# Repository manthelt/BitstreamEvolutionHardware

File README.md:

Bitstream Evolution Dev Board
===
###### Created by Logan Manthey ( [@manthelt](https://github.com/manthelt) )
---

## Introduction

This development board is an extension of the evolvable hardware open source project (https://evolvablehardware.org/). It was created to expand and bring new features to the evolvable hardware ecosystem while still maintaining it’s accessibility. To make the board accessible KiCAD was chosen for the CAD software given it’s open source and free nature. To find Gerber files for printing take a look at the release section. 

## Features

* **Multi-Channel ADC** 
Supporting two 8 channel **NAME OF ADC** ADCs this dev board can record up to 16 channels at up to **XX** samples per second. External ADCs were choose as to free up ports on the nano which would allow for more interrupt input channels to use with experiments such as variance maximization. 

 * **Multi-Channel DAC**
To provide support for future expandability multi channel DACs were included. The primary use case of these DACs is for setting the reference voltage for the the interrupt input on the nano but can be used for other various purposes such as adjusting a voltage offset for the waveform or for setting the reference voltage for the ADCs 

* **Clock Generation**
This Dev Kit also includes a programmable clock generator. The primary uses of this are for both sanity checking instrumentation and for evolving more complex circuits which utilize a waveform as an input source. To allow for this expandability the waveform outputs were left as male jumper pins for easy connection to any section of the board. This will be especially useful when recreating a tone discriminator. There are also multiple channels which are able to be set through software. This allows for more complex experiments to take place which could involve multiple clocks.

## Getting Started and Usage
The following link will take you to the firmware for this project that is to be installed on the nano

### Connecting Channels
To provide the most amount of modulatary each one of the channels on the ADC and each one of connections on the Arduino has a 2 port male connection. By shorting these one can connect channels in varying configurations. The following is an overview of how this connection scheme is archived. 

As one can see both of the connections can be made at the same time. If this is the case and the Arduino is outputting digital outputs then those outputs will be seen on the ADC. 

_Example of Jumper that can be used to short connections (SNT-100-BK-T)_

### Clock Generation
After being set through software the clock generation allows for up to three channels to output a clock. One can simply use a jumper cable to connect to the required section of the board for the experiment at hand.

### DAC Usage
The DACS are also able to be set through software. There are multiple channels to be set as well. 

_Note: The RDY and LDAC outputs are for debugging purposes and made accessible but not highlighted to avoid confusion. To see what these do reference the DAC data sheet found in the data sheets folder_

## Design Methodology 
Overall this design is meant to have as many features as possible while still being accessible. 

### Carrier Board Design
The reasoning behind making this a carrier board instead of fully embedded board was to allow for easy of soldering and to allow the FPGAs to be swapped out to see if there is any physical differences across boards that would affect evolution.

### Clock Generation
The Clock generation section also has male pin outs which allow for flexibility with the configuration. For example you can send in a output from the waveform into a certain input to the FPGA or even send it into the Arduino as an input to sanity check the input values. 

### ADC Section
Given the current platform uses digital serial as the main form of communication there is a temporary data store on the ardunio itself from the ADCs after initiating a data capture. After said capture is complete the data can then be relayed back to the evolution algorithm using the serial lines. Given only one of the channels can be recorded at any given time a decrease in samples per second will occur when capturing more than 1 channel at a given time. This decrease can be seen outlined below in the table. For future expandability a more parallel approach will be needed to increase the samples per second for each one of the channels.  

**A Channels**

|Channels Active|Samples Per Second|
|:-:|:-:|
|1|XXX|
|2|XXX|
|3|XXX|
|4|XXX|
|5|XXX|
|6|XXX|
|7|XXX|
|8|XXX|

<br><br>

**B Channels**

|Channels Active|Samples Per Second|
|:-:|:-:|
|1|XXX|
|2|XXX|
|3|XXX|
|4|XXX|
|5|XXX|
|6|XXX|
|7|XXX|
|8|XXX|

<br><br>

## BOM

|Reference                                                  |Quantity|Value                |Comment                                           |
|-----------------------------------------------------------|--------|---------------------|--------------------------------------------------|
|A1                                                         |1       |Arduino Nano Every   |                                                  |

**Note Data sheets can be found in the datasheets folder**

## Building the Board

## Breakout Boards
To allow for ease of programming many of the parts used in this can be found in prebuilt adafruit breakout boards for testing. These are listed below

* DAC
* ADC
* Clock Generator
* 

### https://github.com/manthelt

Copyright &copy; 2023 [manthelt](https://github.com/manthelt)

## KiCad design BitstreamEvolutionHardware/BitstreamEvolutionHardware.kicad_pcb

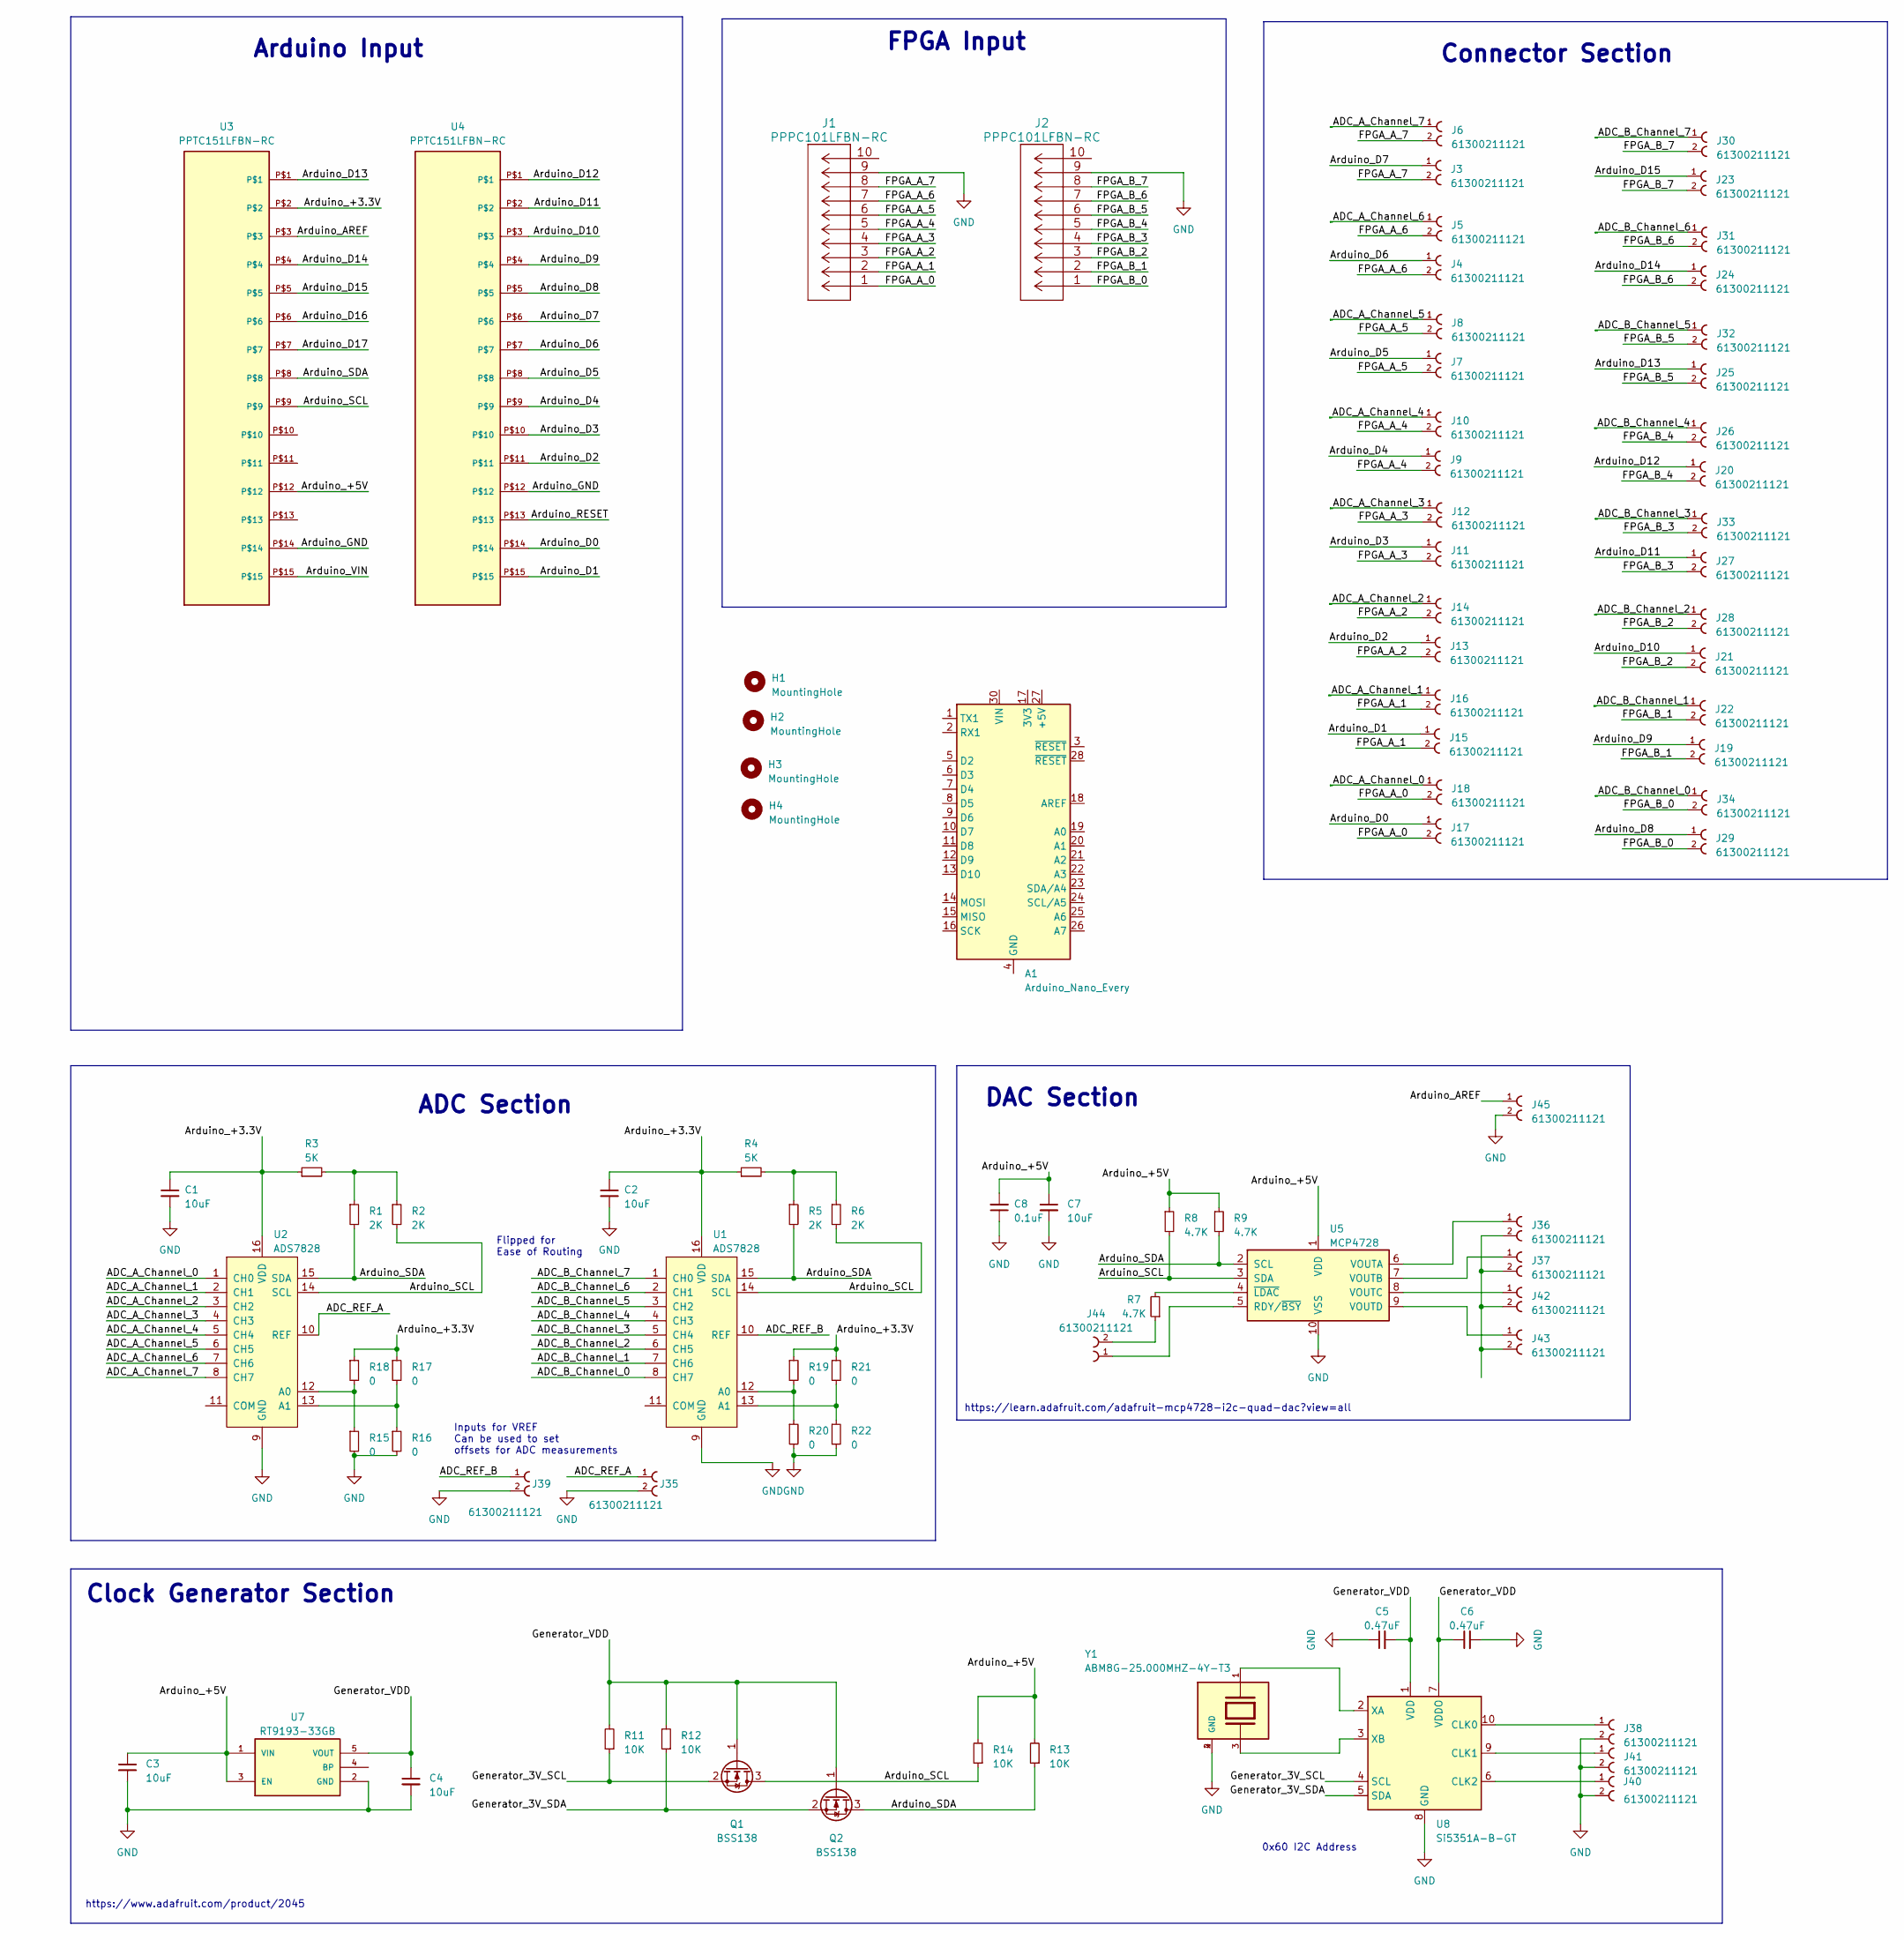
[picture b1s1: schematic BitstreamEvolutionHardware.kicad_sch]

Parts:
A1: Arduino_Nano_Every; Arduino_Nano
C1, C3, C4, C7: 10uF; C_0805_2012Metric
C2: 10uF; R_0805_2012Metric
C5, C6: 0.47uF; R_0805_2012Metric
C8: 0.1uF; C_0805_2012Metric
H1, H2, H3, H4: MountingHole; MountingHole_3.2mm_M3
J1, J2: PPPC101LFBN-RC
J3, J4, J5, J6, J7, J8, J9, J10, J11, J12, J13, J14, J15, J16, J17, J18, J19, J20, J21, J22, J23, J24, J25, J26, J27, J28, J29, J30, J31, J32, J33, J34, J35, J36, J37, J38, J39, J40, J41, J42, J43, J44, J45: 61300211121
Q1, Q2: BSS138; SOT-23
R1, R2, R5, R6: 2K; R_0805_2012Metric
R3, R4: 5K; R_0805_2012Metric
R7, R8, R9: 4.7K; R_0805_2012Metric
R11, R12, R13, R14: 10K; R_0805_2012Metric
R15, R16, R17, R18, R19, R20, R21, R22: 0; R_0805_2012Metric
U1, U2: ADS7828; TSSOP-16_4.4x5mm_P0.65mm
U3, U4: PPTC151LFBN-RC
U5: MCP4728; MSOP-10_3x3mm_P0.5mm
U7: RT9193-33GB; SOT94P279X129-5N
U8: Si5351A-B-GT; MSOP-10_3x3mm_P0.5mm
Y1: ABM8G-25.000MHZ-4Y-T3; XTAL_ABM8G-25.000MHZ-4Y-T3; PARTREV 08.13.15

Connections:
/ADC_A_Channel_0: J18.1, U2.1 (CH0)
/ADC_A_Channel_1: J16.1, U2.2 (CH1)
/ADC_A_Channel_2: J14.1, U2.3 (CH2)
/ADC_A_Channel_3: J12.1, U2.4 (CH3)
/ADC_A_Channel_4: J10.1, U2.5 (CH4)
/ADC_A_Channel_5: J8.1, U2.6 (CH5)
/ADC_A_Channel_6: J5.1, U2.7 (CH6)
/ADC_A_Channel_7: J6.1, U2.8 (CH7)
/ADC_B_Channel_0: J34.1, U1.8 (CH7)
/ADC_B_Channel_1: J22.1, U1.7 (CH6)
/ADC_B_Channel_2: J28.1, U1.6 (CH5)
/ADC_B_Channel_3: J33.1, U1.5 (CH4)
/ADC_B_Channel_4: J26.1, U1.4 (CH3)
/ADC_B_Channel_5: J32.1, U1.3 (CH2)
/ADC_B_Channel_6: J31.1, U1.2 (CH1)
/ADC_B_Channel_7: J30.1, U1.1 (CH0)
/ADC_REF_A: J35.1, U2.10 (REF)
/ADC_REF_B: J39.1, U1.10 (REF)
/Arduino_+3.3V: C1.1, C2.1, R3.1, R4.1, R17.1, R18.1, R19.1, R21.1, U1.16 (VDD), U2.16 (VDD), U3.P$2
/Arduino_+5V: C3.1, C7.1, C8.2, R8.1, R9.1, R13.2, R14.2, U3.P$12, U5.1 (VDD), U7.1 (VIN), U7.3 (EN)
/Arduino_AREF: J45.1, U3.P$3
/Arduino_D0: J17.1, U4.P$14
/Arduino_D1: J15.1, U4.P$15
/Arduino_D2: J13.1, U4.P$11
/Arduino_D3: J11.1, U4.P$10
/Arduino_D4: J9.1, U4.P$9
/Arduino_D5: J7.1, U4.P$8
/Arduino_D6: J4.1, U4.P$7
/Arduino_D7: J3.1, U4.P$6
/Arduino_D8: J29.1, U4.P$5
/Arduino_D9: J19.1, U4.P$4
/Arduino_D10: J21.1, U4.P$3
/Arduino_D11: J27.1, U4.P$2
/Arduino_D12: J20.1, U4.P$1
/Arduino_D13: J25.1, U3.P$1
/Arduino_D14: J24.1, U3.P$4
/Arduino_D15: J23.1, U3.P$5
/Arduino_D16: U3.P$6
/Arduino_D17: U3.P$7
/Arduino_GND: U3.P$14, U4.P$12
/Arduino_RESET: U4.P$13
/Arduino_SCL: Q1.3 (D), R2.2, R6.2, R8.2, R14.1, U1.14 (SCL), U2.14 (SCL), U3.P$9, U5.3 (SDA)
/Arduino_SDA: Q2.3 (D), R1.2, R5.2, R9.2, R13.1, U1.15 (SDA), U2.15 (SDA), U3.P$8, U5.2 (SCL)
/Arduino_VIN: U3.P$15
/FPGA_A_0: J1.1, J17.2, J18.2
/FPGA_A_1: J1.2, J15.2, J16.2
/FPGA_A_2: J1.3, J13.2, J14.2
/FPGA_A_3: J1.4, J11.2, J12.2
/FPGA_A_4: J1.5, J9.2, J10.2
/FPGA_A_5: J1.6, J7.2, J8.2
/FPGA_A_6: J1.7, J4.2, J5.2
/FPGA_A_7: J1.8, J3.2, J6.2
/FPGA_B_0: J2.1, J29.2, J34.2
/FPGA_B_1: J2.2, J19.2, J22.2
/FPGA_B_2: J2.3, J21.2, J28.2
/FPGA_B_3: J2.4, J27.2, J33.2
/FPGA_B_4: J2.5, J20.2, J26.2
/FPGA_B_5: J2.6, J25.2, J32.2
/FPGA_B_6: J2.7, J24.2, J31.2
/FPGA_B_7: J2.8, J23.2, J30.2
/Generator_3V_SCL: Q1.2 (S), R11.1, U8.4 (SCL)
/Generator_3V_SDA: Q2.2 (S), R12.1, U8.5 (SDA)
/Generator_VDD: C4.1, C5.2, C6.1, Q1.1 (G), Q2.1 (G), R11.2, R12.2, U7.5 (VOUT), U8.1 (VDD), U8.7 (VDDO)
GND: C1.2, C2.2, C3.2, C4.2, C5.1, C6.2, C7.2, C8.1, J1.9, J2.9, J35.2, J38.2, J39.2, J40.2, J41.2, J45.2, R15.2, R16.2, R20.2, R22.2, U1.9 (GND), U2.9 (GND), U5.10 (VSS), U7.2 (GND), U8.8 (GND), Y1.2 (GND), Y1.4 (GND)
unnamed: A1.4 (GND), A1.29 (GND)
unnamed: J36.2, J37.2, J42.2, J43.2
unnamed: J44.2, R7.1
unnamed: R1.1, R2.1, R3.2
unnamed: R4.2, R5.1, R6.1
unnamed: R19.2, R20.1, U1.12 (A0)
unnamed: R21.2, R22.1, U1.13 (A1)
unnamed: R15.1, R18.2, U2.12 (A0)
unnamed: R16.1, R17.2, U2.13 (A1)
unnamed: J44.1, U5.5 (RDY/~BSY)
unnamed: J36.1, U5.6 (VOUTA)
unnamed: J37.1, U5.7 (VOUTB)
unnamed: J42.1, U5.8 (VOUTC)
unnamed: J43.1, U5.9 (VOUTD)
unnamed: R7.2, U5.4 (~LDAC)
unnamed: J38.1, U8.10 (CLK0)
unnamed: J41.1, U8.9 (CLK1)
unnamed: J40.1, U8.6 (CLK2)
unnamed: U8.2 (XA), Y1.1
unnamed: U8.3 (XB), Y1.3

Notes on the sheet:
ADC Section
https://learn.adafruit.com/adafruit-mcp4728-i2c-quad-dac?view=all
Arduino Input
Flipped for Ease of Routing
Connector Section
DAC Section
https://www.adafruit.com/product/2045
Clock Generator Section
FPGA Input
Inputs for VREF Can be used to set offsets for ADC measurements
0x60 I2C Address

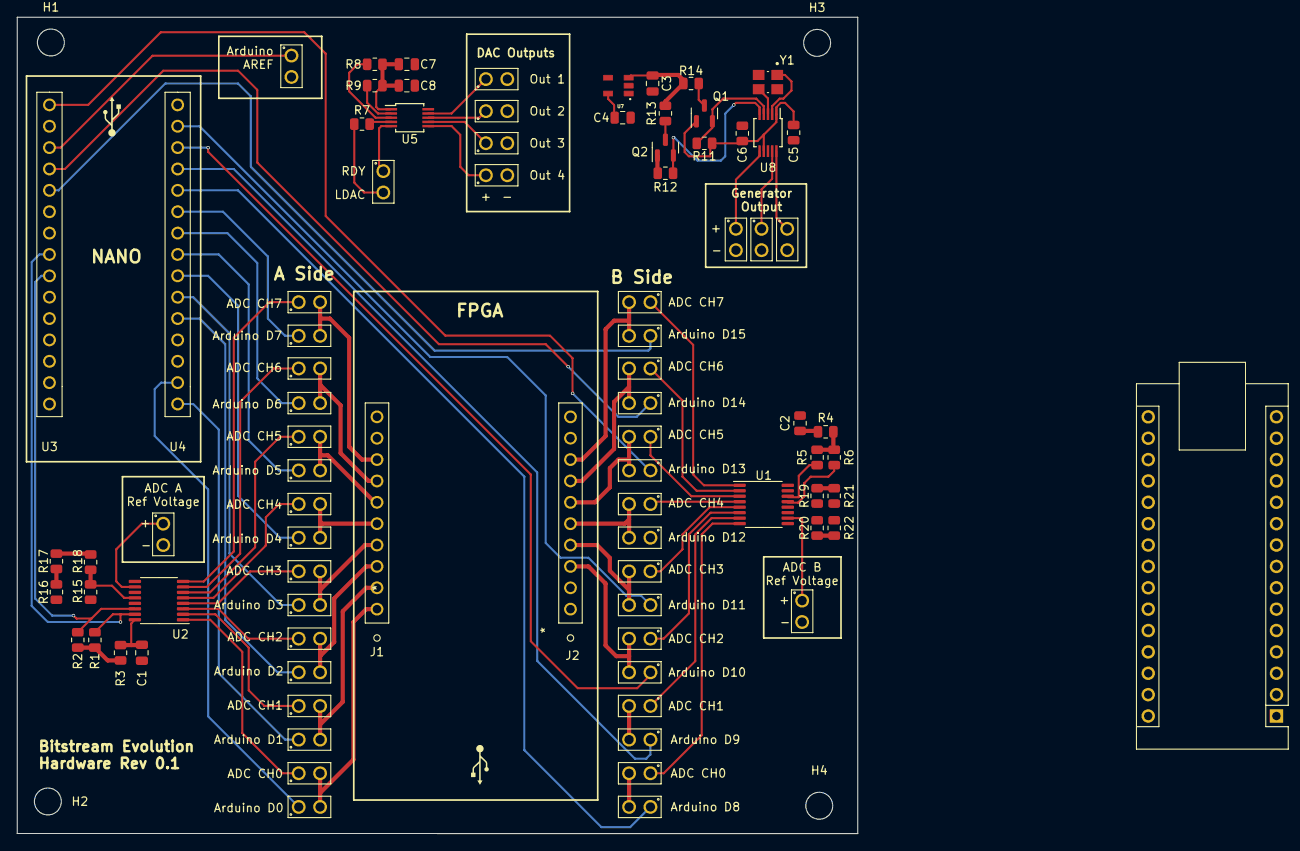
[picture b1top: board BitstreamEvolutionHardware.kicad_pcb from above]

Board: 4 copper layers, 99.9 x 97.0 mm, 89 parts (0 on the bottom side), 80 nets.

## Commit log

2023-02-16 Added Parts to Lib
2023-02-16 Added Connectors Section to Sch and Linked Footprints
2023-02-16 Rev 0.1 Rough Draft Done
2023-02-16 Added Pictures
2023-02-28 update formatting
2023-02-28 added link to evhardware website
2023-03-16 Backup
2023-03-16 Almost Done with Routing, need to route power and I2C Lines
2023-03-21 Added Datasheet Pdfs
2023-03-21 Added Datasheets PDFs
2023-03-28 Lab 6 Complete Need to Clean Up

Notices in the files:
BitstreamEvolutionHardware/BitstreamEvolutionHardware.kicad_pcb:
CC-BY-SA
parts and their libraries:
Copyright 2021 Accelerated Designs. All rights reserved.
